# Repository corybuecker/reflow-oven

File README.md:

# reflow-oven
The plans, BoM, instructions, etc. for a soldering reflow oven. Please note that this requires an ESP32 C6 microcontroller and a thermocouple amplifier.

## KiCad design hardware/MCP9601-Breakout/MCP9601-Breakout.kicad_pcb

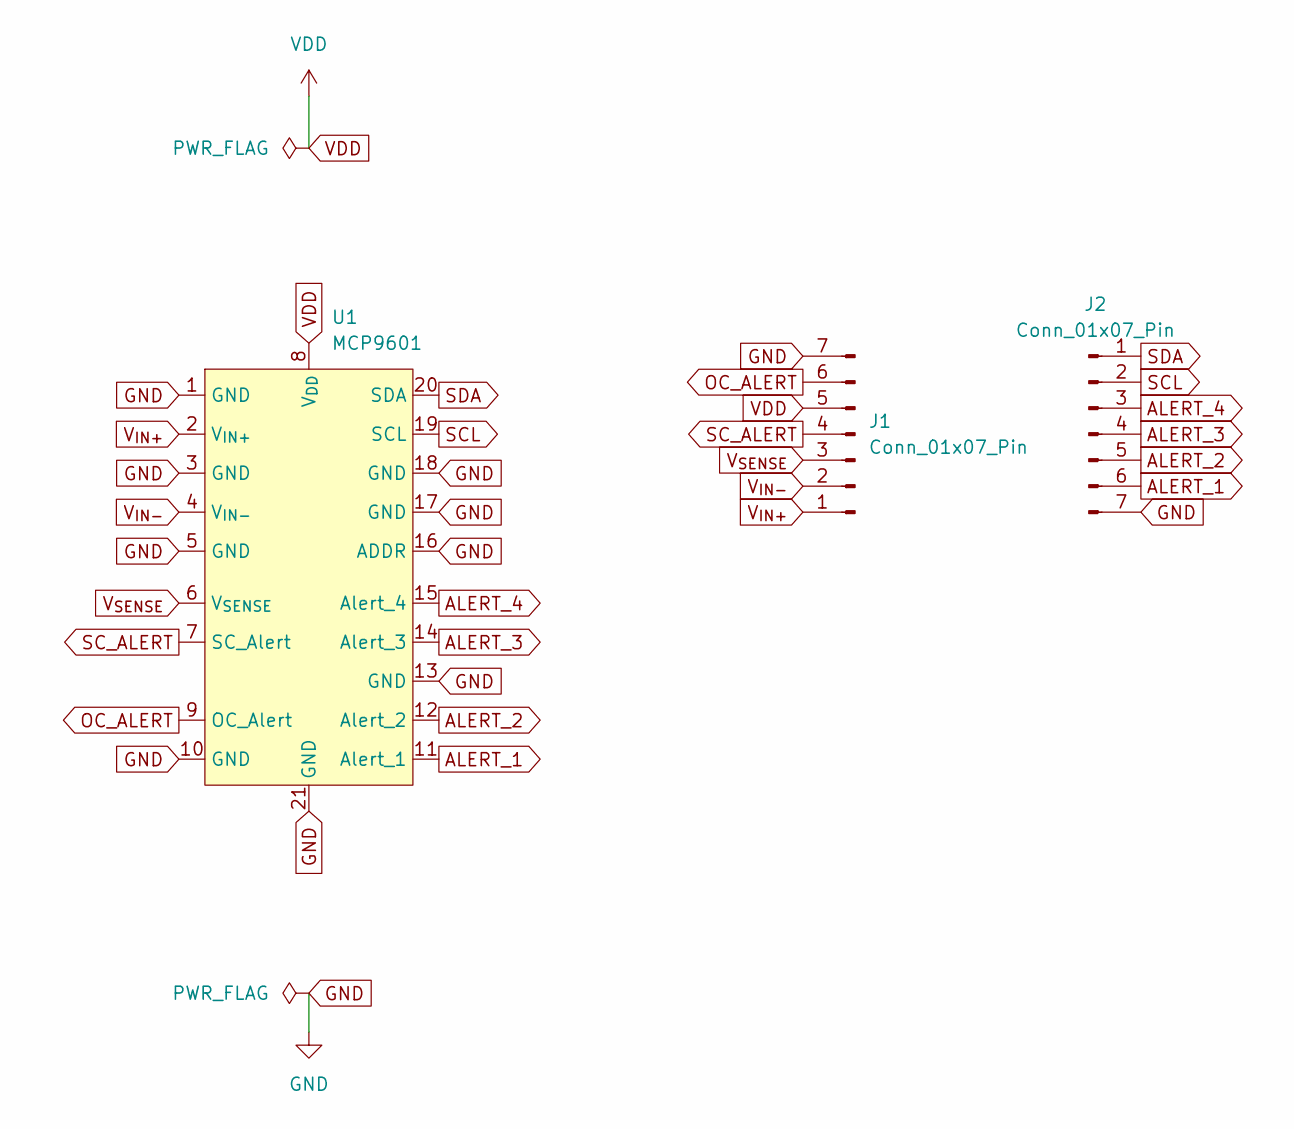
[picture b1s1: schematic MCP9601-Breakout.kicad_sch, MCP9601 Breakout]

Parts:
J1, J2: Conn_01x07_Pin; PinHeader_1x07_P2.54mm_Vertical
U1: MCP9601

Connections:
ALERT_1: J2.6, U1.11 (Alert_1)
ALERT_2: J2.5, U1.12 (Alert_2)
ALERT_3: J2.4, U1.14 (Alert_3)
ALERT_4: J2.3, U1.15 (Alert_4)
GND: J1.7, J2.7, U1.1 (GND), U1.3 (GND), U1.5 (GND), U1.10 (GND), U1.13 (GND), U1.16 (ADDR), U1.17 (GND), U1.18 (GND), U1.21 (GND)
OC_ALERT: J1.6, U1.9 (OC_Alert)
SCL: J2.2, U1.19 (SCL)
SC_ALERT: J1.4, U1.7 (SC_Alert)
SDA: J2.1, U1.20 (SDA)
VDD: J1.5, U1.8 (V_{DD})
V_{IN+}: J1.1, U1.2 (V_{IN+})
V_{IN-}: J1.2, U1.4 (V_{IN-})
V_{SENSE}: J1.3, U1.6 (V_{SENSE})

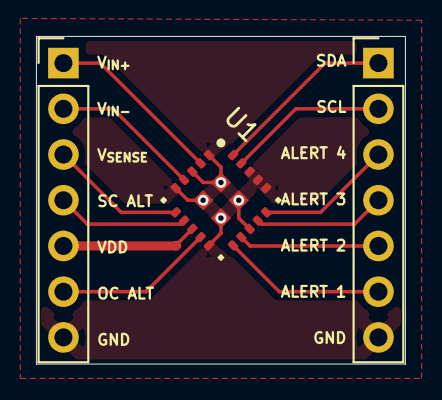
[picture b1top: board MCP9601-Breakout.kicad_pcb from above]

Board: 2 copper layers, 20.5 x 18.2 mm, 3 parts (0 on the bottom side), 13 nets.

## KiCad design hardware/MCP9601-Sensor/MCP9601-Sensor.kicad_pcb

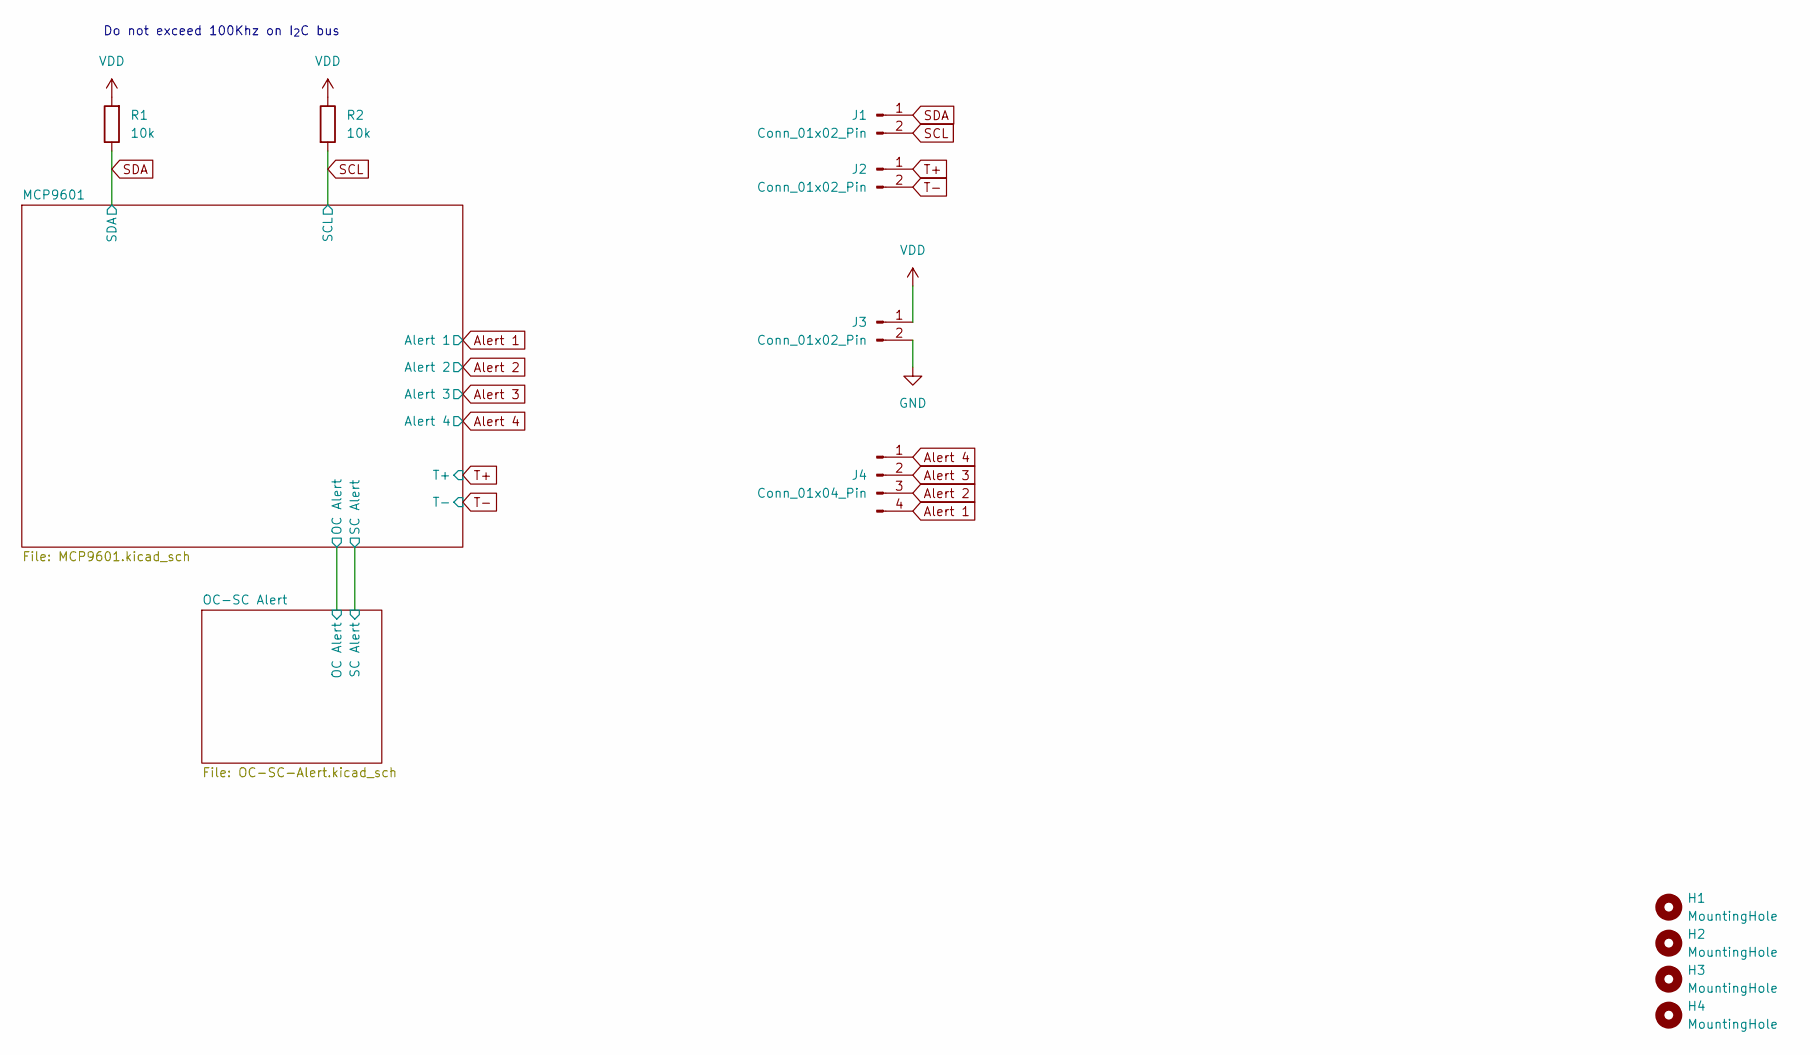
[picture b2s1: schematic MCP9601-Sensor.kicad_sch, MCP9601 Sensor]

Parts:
H1, H2, H3, H4: MountingHole; MountingHole_3.2mm_M3
J1, J2, J3: Conn_01x02_Pin; PinHeader_1x02_P2.54mm_Vertical
J4: Conn_01x04_Pin; PinHeader_1x04_P2.54mm_Vertical
R1, R2: 10k; R_0805_2012Metric; DigiKey Part Number 311-10.0KCRCT-ND

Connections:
Alert 1: J4.4; also elsewhere on the board
Alert 2: J4.3; also elsewhere on the board
Alert 3: J4.2; also elsewhere on the board
Alert 4: J4.1; also elsewhere on the board
GND: J3.2; also elsewhere on the board
SCL: J1.2, R2.2; also elsewhere on the board
SDA: J1.1, R1.1; also elsewhere on the board
T+: J2.1; also elsewhere on the board
T-: J2.2; also elsewhere on the board
VDD: J3.1, R1.2, R2.1; also elsewhere on the board

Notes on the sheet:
Do not exceed 100Khz on I_{2}C bus

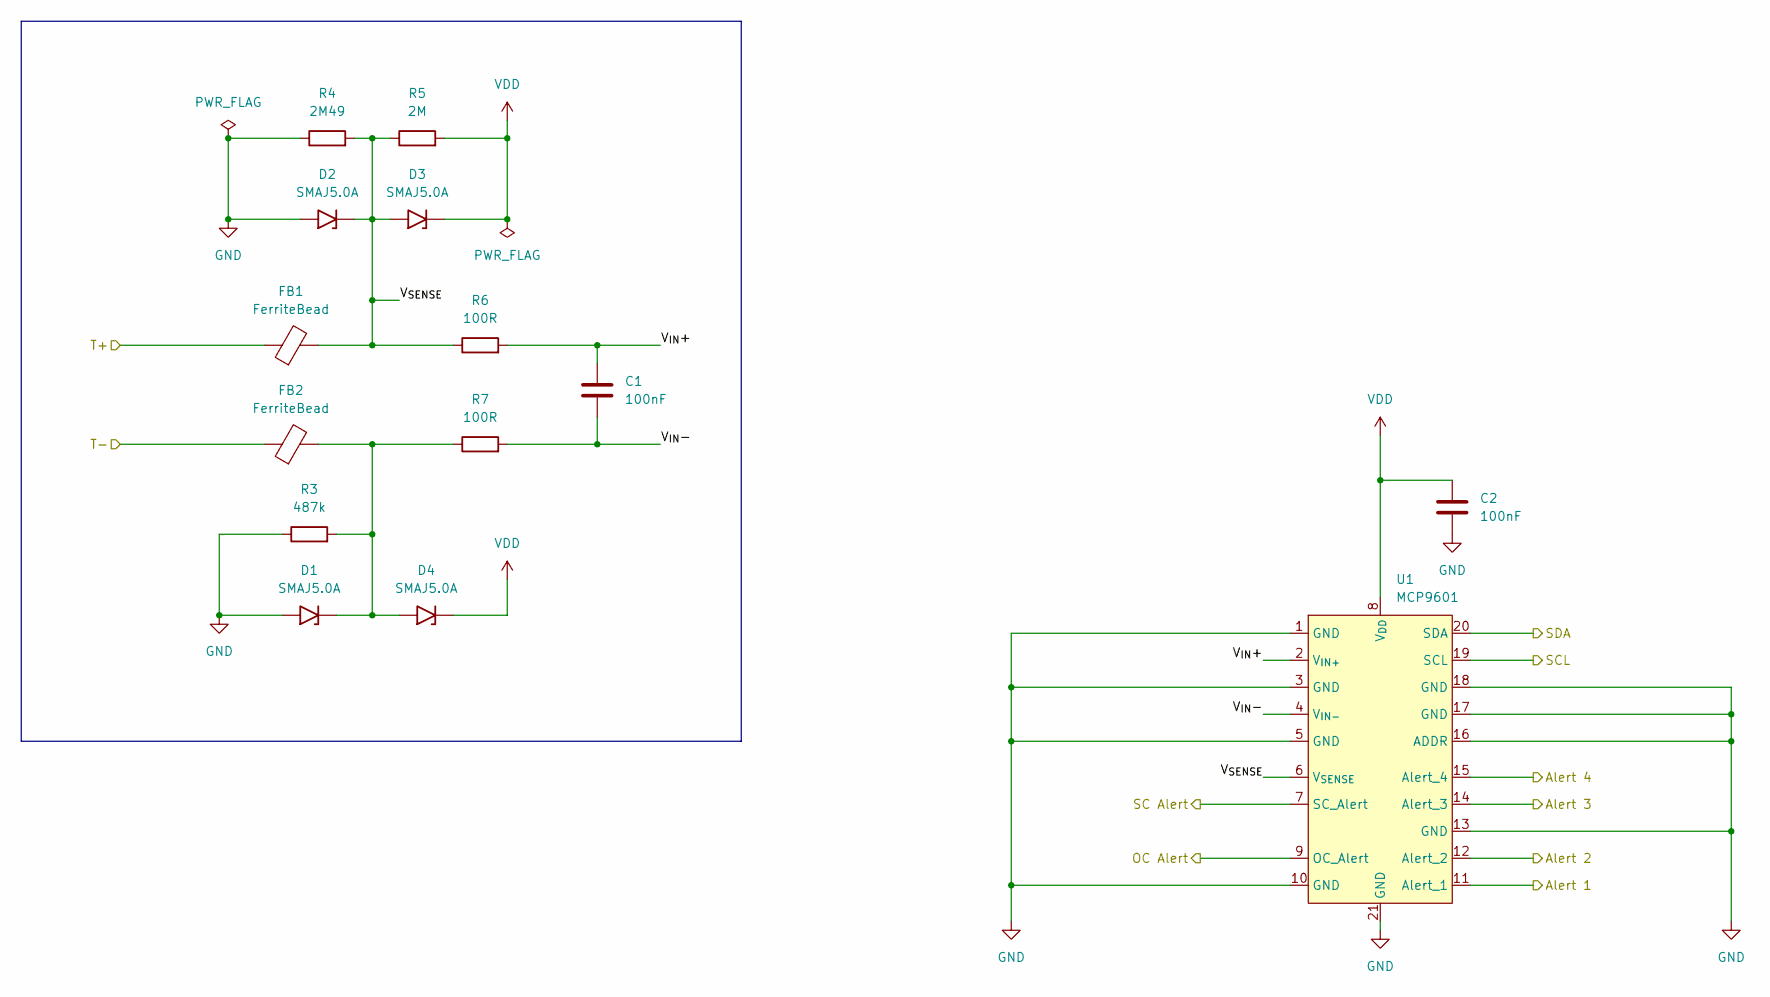
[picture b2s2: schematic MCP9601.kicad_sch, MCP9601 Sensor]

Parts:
C1, C2: 100nF; C_0805_2012Metric; DigiKey Part Number 311-1140-1-ND
D1, D2, D3, D4: SMAJ5.0A; DigiKey Part Number SMAJ5.0A-E3/61GICT-ND
FB1, FB2: FerriteBead; L_0805_2012Metric; DigiKey Part Number 240-2399-1-ND
R3: 487k; R_0805_2012Metric; DigiKey Part Number 311-487KCRCT-ND
R4: 2M49; R_0805_2012Metric; DigiKey Part Number 311-2.49MCRCT-ND
R5: 2M; R_0805_2012Metric; DigiKey Part Number 541-4129-1-ND
R6, R7: 100R; R_0805_2012Metric; DigiKey Part Number 311-100CRCT-ND
U1: MCP9601; DigiKey Part Number 150-MCP9601T-E/MXCT-ND

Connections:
/MCP9601/OC Alert: U1.9 (OC_Alert); also elsewhere on the board
/MCP9601/SC Alert: U1.7 (SC_Alert); also elsewhere on the board
/MCP9601/V_{IN}+: C1.1, R6.2, U1.2 (V_{IN+})
/MCP9601/V_{IN}-: C1.2, R7.2, U1.4 (V_{IN-})
/MCP9601/V_{SENSE}: D2.2 (Cathode), D3.1 (Anode), FB1.2, R4.2, R5.1, R6.1, U1.6 (V_{SENSE})
Alert 1: U1.11 (Alert_1); also elsewhere on the board
Alert 2: U1.12 (Alert_2); also elsewhere on the board
Alert 3: U1.14 (Alert_3); also elsewhere on the board
Alert 4: U1.15 (Alert_4); also elsewhere on the board
GND: C2.2, D1.1 (Anode), D2.1 (Anode), R3.1, R4.1, U1.1 (GND), U1.3 (GND), U1.5 (GND), U1.10 (GND), U1.13 (GND), U1.16 (ADDR), U1.17 (GND), U1.18 (GND), U1.21 (GND); also elsewhere on the board
unnamed: D1.2 (Cathode), D4.1 (Anode), FB2.2, R3.2, R7.1
SCL: U1.19 (SCL); also elsewhere on the board
SDA: U1.20 (SDA); also elsewhere on the board
T+: FB1.1; also elsewhere on the board
T-: FB2.1; also elsewhere on the board
VDD: C2.1, D3.2 (Cathode), D4.2 (Cathode), R5.2, U1.8 (V_{DD}); also elsewhere on the board

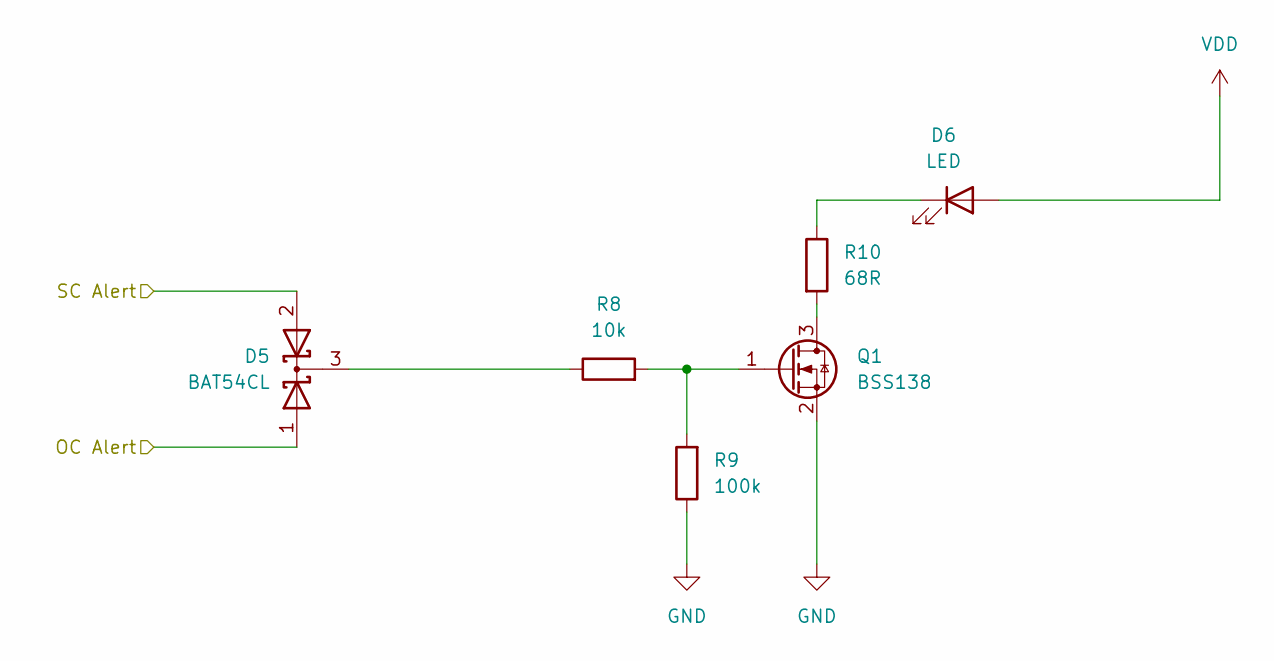
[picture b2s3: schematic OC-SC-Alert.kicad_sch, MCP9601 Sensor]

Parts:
D5: BAT54CL; DigiKey Part Number BAT54CLT3GOSCT-ND
D6: LED; LED_0805_2012Metric; DigiKey Part Number 160-1427-1-ND
Q1: BSS138; DigiKey Part Number BSS138CT-ND
R8: 10k; R_0805_2012Metric; DigiKey Part Number 311-10.0KCRCT-ND
R9: 100k; R_0805_2012Metric; DigiKey Part Number 311-100KARCT-ND
R10: 68R; R_0805_2012Metric; DigiKey Part Number 311-68ARCT-ND

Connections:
/MCP9601/OC Alert: D5.1 (A); also elsewhere on the board
/MCP9601/SC Alert: D5.2 (A); also elsewhere on the board
GND: Q1.2 (S), R9.1; also elsewhere on the board
unnamed: D5.3 (K), R8.1
unnamed: D6.1 (K), R10.1
unnamed: Q1.3 (D), R10.2
unnamed: Q1.1 (G), R8.2, R9.2
VDD: D6.2 (A); also elsewhere on the board

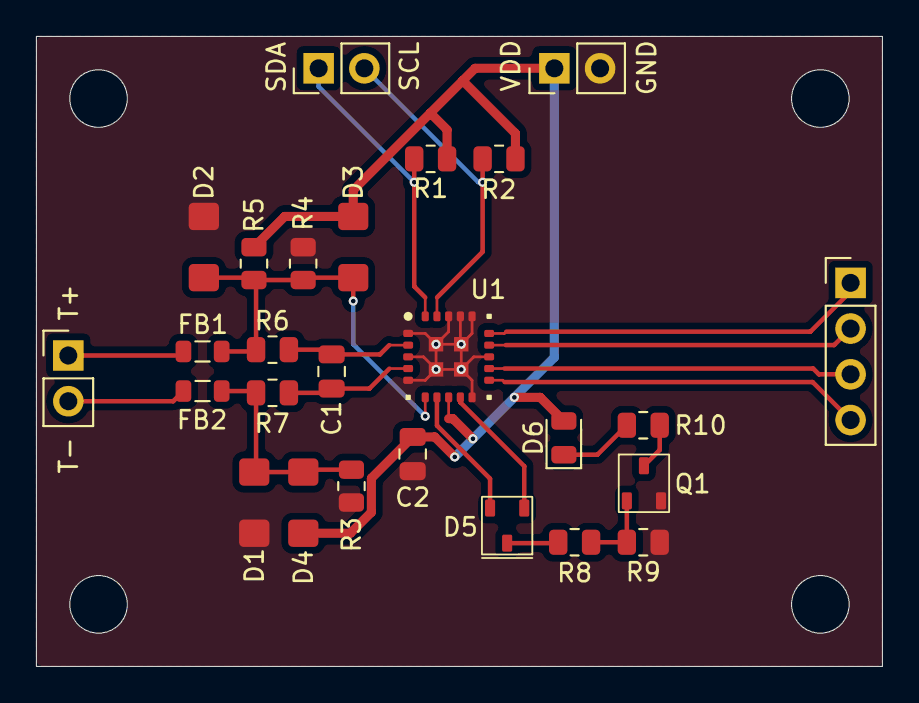
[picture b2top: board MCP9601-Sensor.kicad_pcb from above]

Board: 2 copper layers, 47.0 x 35.0 mm, 30 parts (0 on the bottom side), 20 nets.

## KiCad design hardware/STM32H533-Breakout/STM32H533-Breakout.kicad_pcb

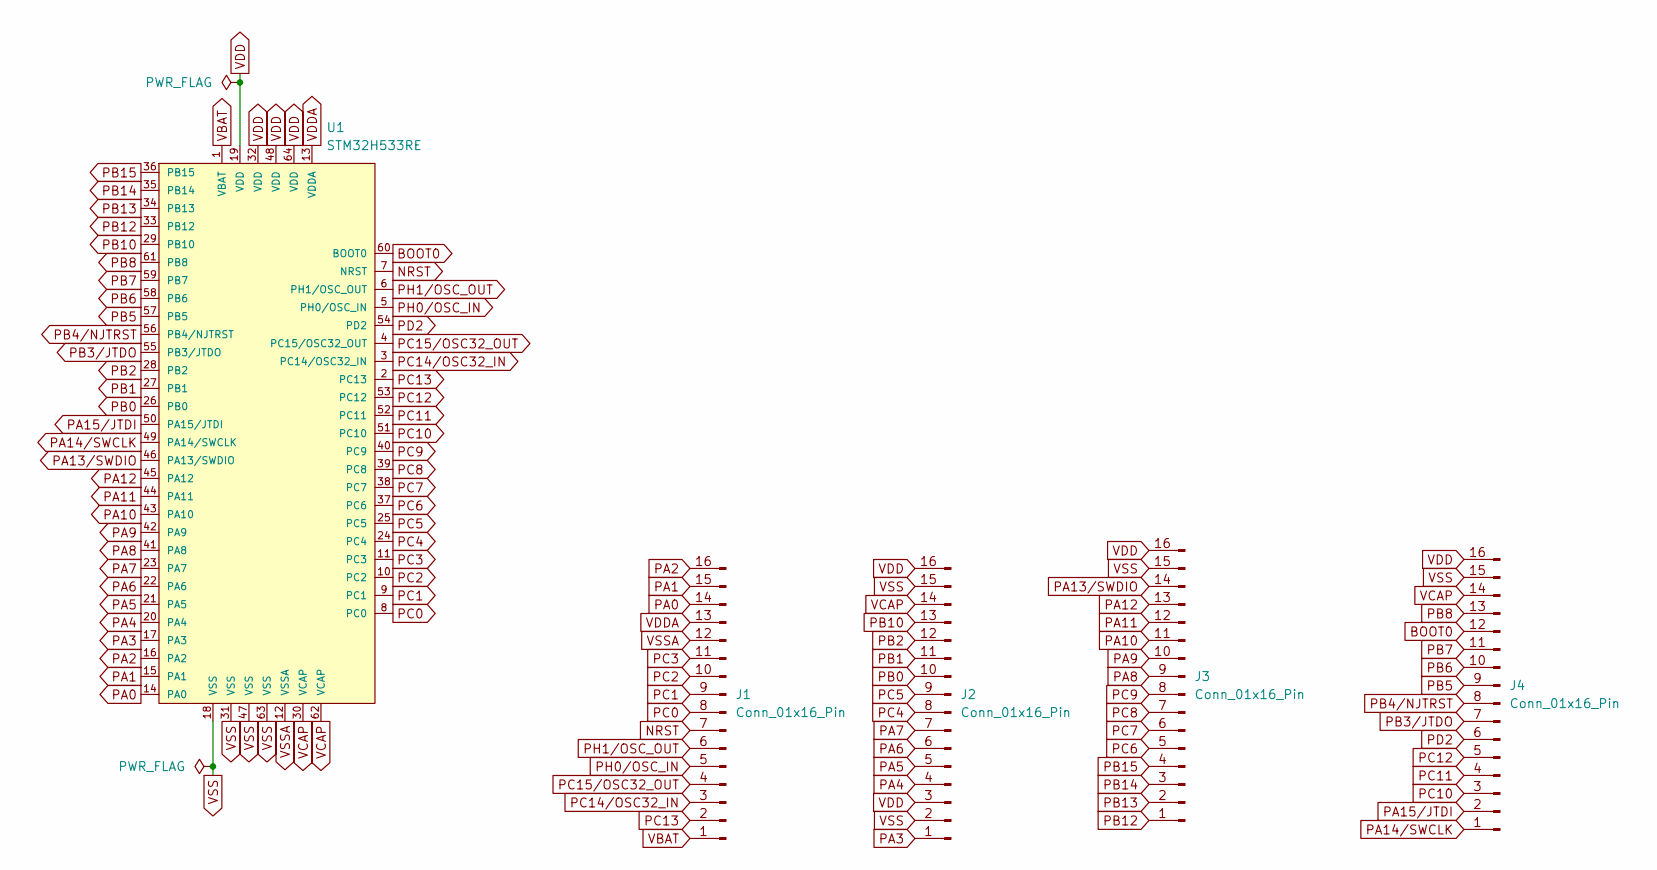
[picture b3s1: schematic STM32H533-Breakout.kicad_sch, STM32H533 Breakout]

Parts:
J1, J2, J3, J4: Conn_01x16_Pin; PinHeader_1x16_P2.54mm_Vertical
U1: STM32H533RE

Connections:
BOOT0: J4.12, U1.60 (BOOT0)
NRST: J1.7, U1.7 (NRST)
PA0: J1.14, U1.14 (PA0)
PA1: J1.15, U1.15 (PA1)
PA2: J1.16, U1.16 (PA2)
PA3: J2.1, U1.17 (PA3)
PA4: J2.4, U1.20 (PA4)
PA5: J2.5, U1.21 (PA5)
PA6: J2.6, U1.22 (PA6)
PA7: J2.7, U1.23 (PA7)
PA8: J3.9, U1.41 (PA8)
PA9: J3.10, U1.42 (PA9)
PA10: J3.11, U1.43 (PA10)
PA11: J3.12, U1.44 (PA11)
PA12: J3.13, U1.45 (PA12)
PA13/SWDIO: J3.14, U1.46 (PA13/SWDIO)
PA14/SWCLK: J4.1, U1.49 (PA14/SWCLK)
PA15/JTDI: J4.2, U1.50 (PA15/JTDI)
PB0: J2.10, U1.26 (PB0)
PB1: J2.11, U1.27 (PB1)
PB2: J2.12, U1.28 (PB2)
PB3/JTDO: J4.7, U1.55 (PB3/JTDO)
PB4/NJTRST: J4.8, U1.56 (PB4/NJTRST)
PB5: J4.9, U1.57 (PB5)
PB6: J4.10, U1.58 (PB6)
PB7: J4.11, U1.59 (PB7)
PB8: J4.13, U1.61 (PB8)
PB10: J2.13, U1.29 (PB10)
PB12: J3.1, U1.33 (PB12)
PB13: J3.2, U1.34 (PB13)
PB14: J3.3, U1.35 (PB14)
PB15: J3.4, U1.36 (PB15)
PC0: J1.8, U1.8 (PC0)
PC1: J1.9, U1.9 (PC1)
PC2: J1.10, U1.10 (PC2)
PC3: J1.11, U1.11 (PC3)
PC4: J2.8, U1.24 (PC4)
PC5: J2.9, U1.25 (PC5)
PC6: J3.5, U1.37 (PC6)
PC7: J3.6, U1.38 (PC7)
PC8: J3.7, U1.39 (PC8)
PC9: J3.8, U1.40 (PC9)
PC10: J4.3, U1.51 (PC10)
PC11: J4.4, U1.52 (PC11)
PC12: J4.5, U1.53 (PC12)
PC13: J1.2, U1.2 (PC13)
PC14/OSC32_IN: J1.3, U1.3 (PC14/OSC32_IN)
PC15/OSC32_OUT: J1.4, U1.4 (PC15/OSC32_OUT)
PD2: J4.6, U1.54 (PD2)
PH0/OSC_IN: J1.5, U1.5 (PH0/OSC_IN)
PH1/OSC_OUT: J1.6, U1.6 (PH1/OSC_OUT)
VBAT: J1.1, U1.1 (VBAT)
VCAP: J2.14, J4.14, U1.30 (VCAP), U1.62 (VCAP)
VDD: J2.3, J2.16, J3.16, J4.16, U1.19 (VDD), U1.32 (VDD), U1.48 (VDD), U1.64 (VDD)
VDDA: J1.13, U1.13 (VDDA)
VSS: J2.2, J2.15, J3.15, J4.15, U1.18 (VSS), U1.31 (VSS), U1.47 (VSS), U1.63 (VSS)
VSSA: J1.12, U1.12 (VSSA)

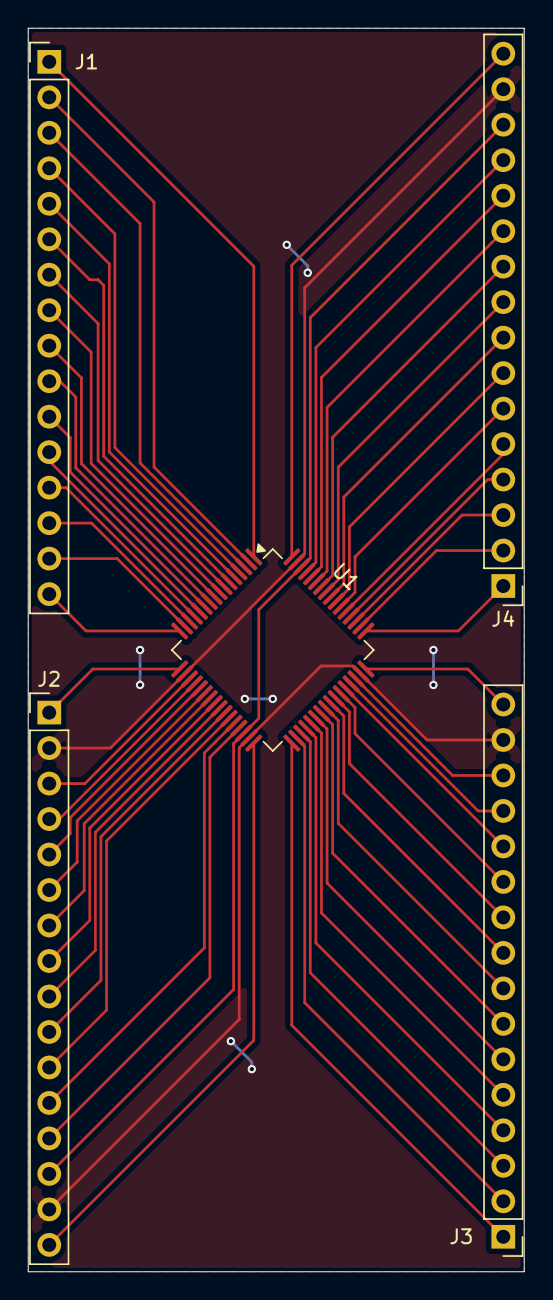
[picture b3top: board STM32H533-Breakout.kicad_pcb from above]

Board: 2 copper layers, 35.5 x 89.0 mm, 5 parts (0 on the bottom side), 57 nets.

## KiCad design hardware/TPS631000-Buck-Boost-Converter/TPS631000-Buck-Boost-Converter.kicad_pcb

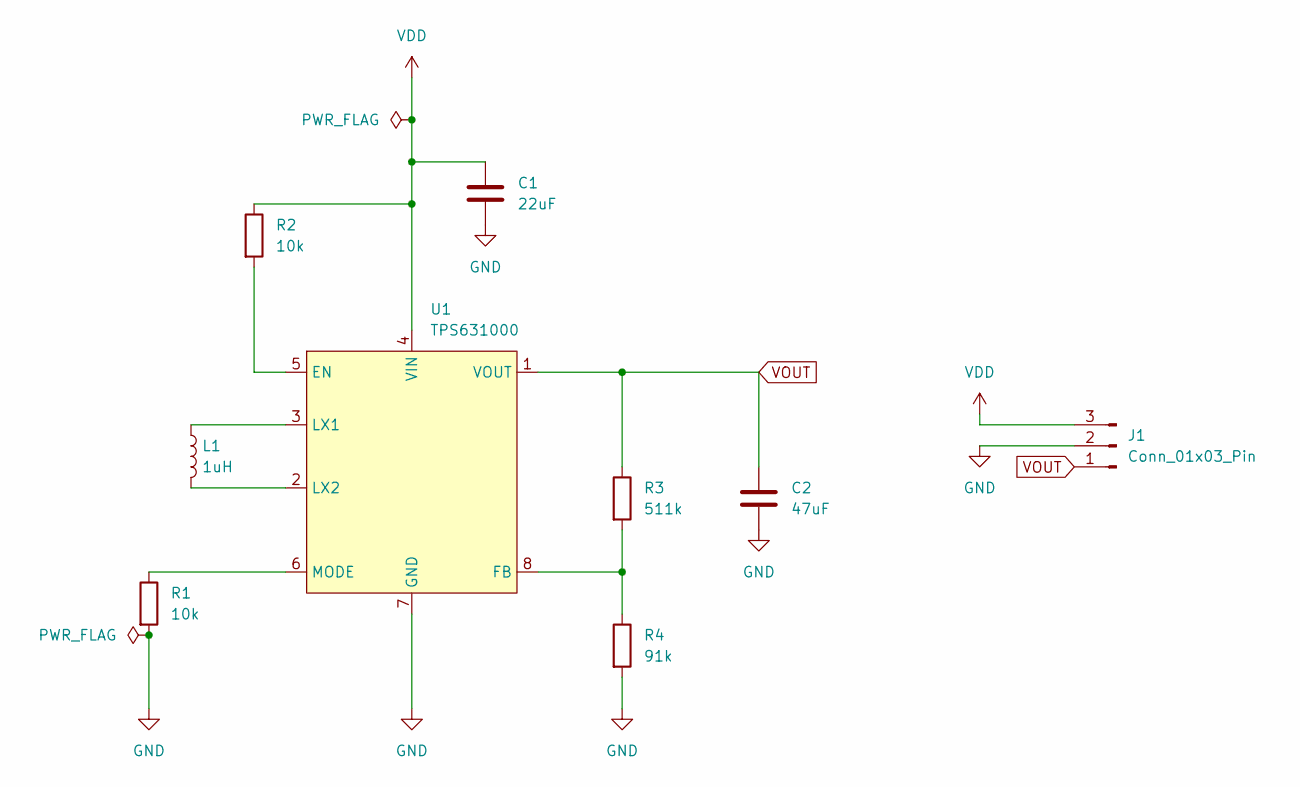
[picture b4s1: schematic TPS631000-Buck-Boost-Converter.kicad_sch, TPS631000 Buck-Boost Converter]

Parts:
C1: 22uF; C_0805_2012Metric
C2: 47uF; C_0805_2012Metric
J1: Conn_01x03_Pin; PinHeader_1x03_P2.54mm_Vertical
L1: 1uH; L_0805_2012Metric
R1, R2: 10k; R_0805_2012Metric
R3: 511k; R_0805_2012Metric
R4: 91k; R_0805_2012Metric
U1: TPS631000

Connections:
GND: C1.2, C2.2, J1.2, R1.2, R4.2, U1.7 (GND)
unnamed: R2.2, U1.5 (EN)
unnamed: R3.2, R4.1, U1.8 (FB)
unnamed: L1.1, U1.3 (LX1)
unnamed: L1.2, U1.2 (LX2)
unnamed: R1.1, U1.6 (MODE)
VDD: C1.1, J1.3, R2.1, U1.4 (VIN)
VOUT: C2.1, J1.1, R3.1, U1.1 (VOUT)

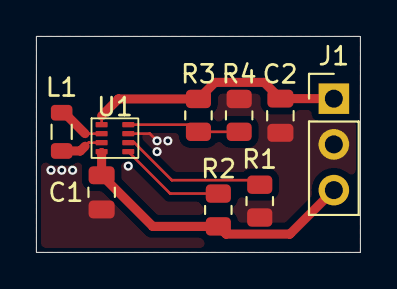
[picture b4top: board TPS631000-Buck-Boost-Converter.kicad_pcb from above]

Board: 2 copper layers, 18.0 x 12.0 mm, 9 parts (0 on the bottom side), 8 nets.

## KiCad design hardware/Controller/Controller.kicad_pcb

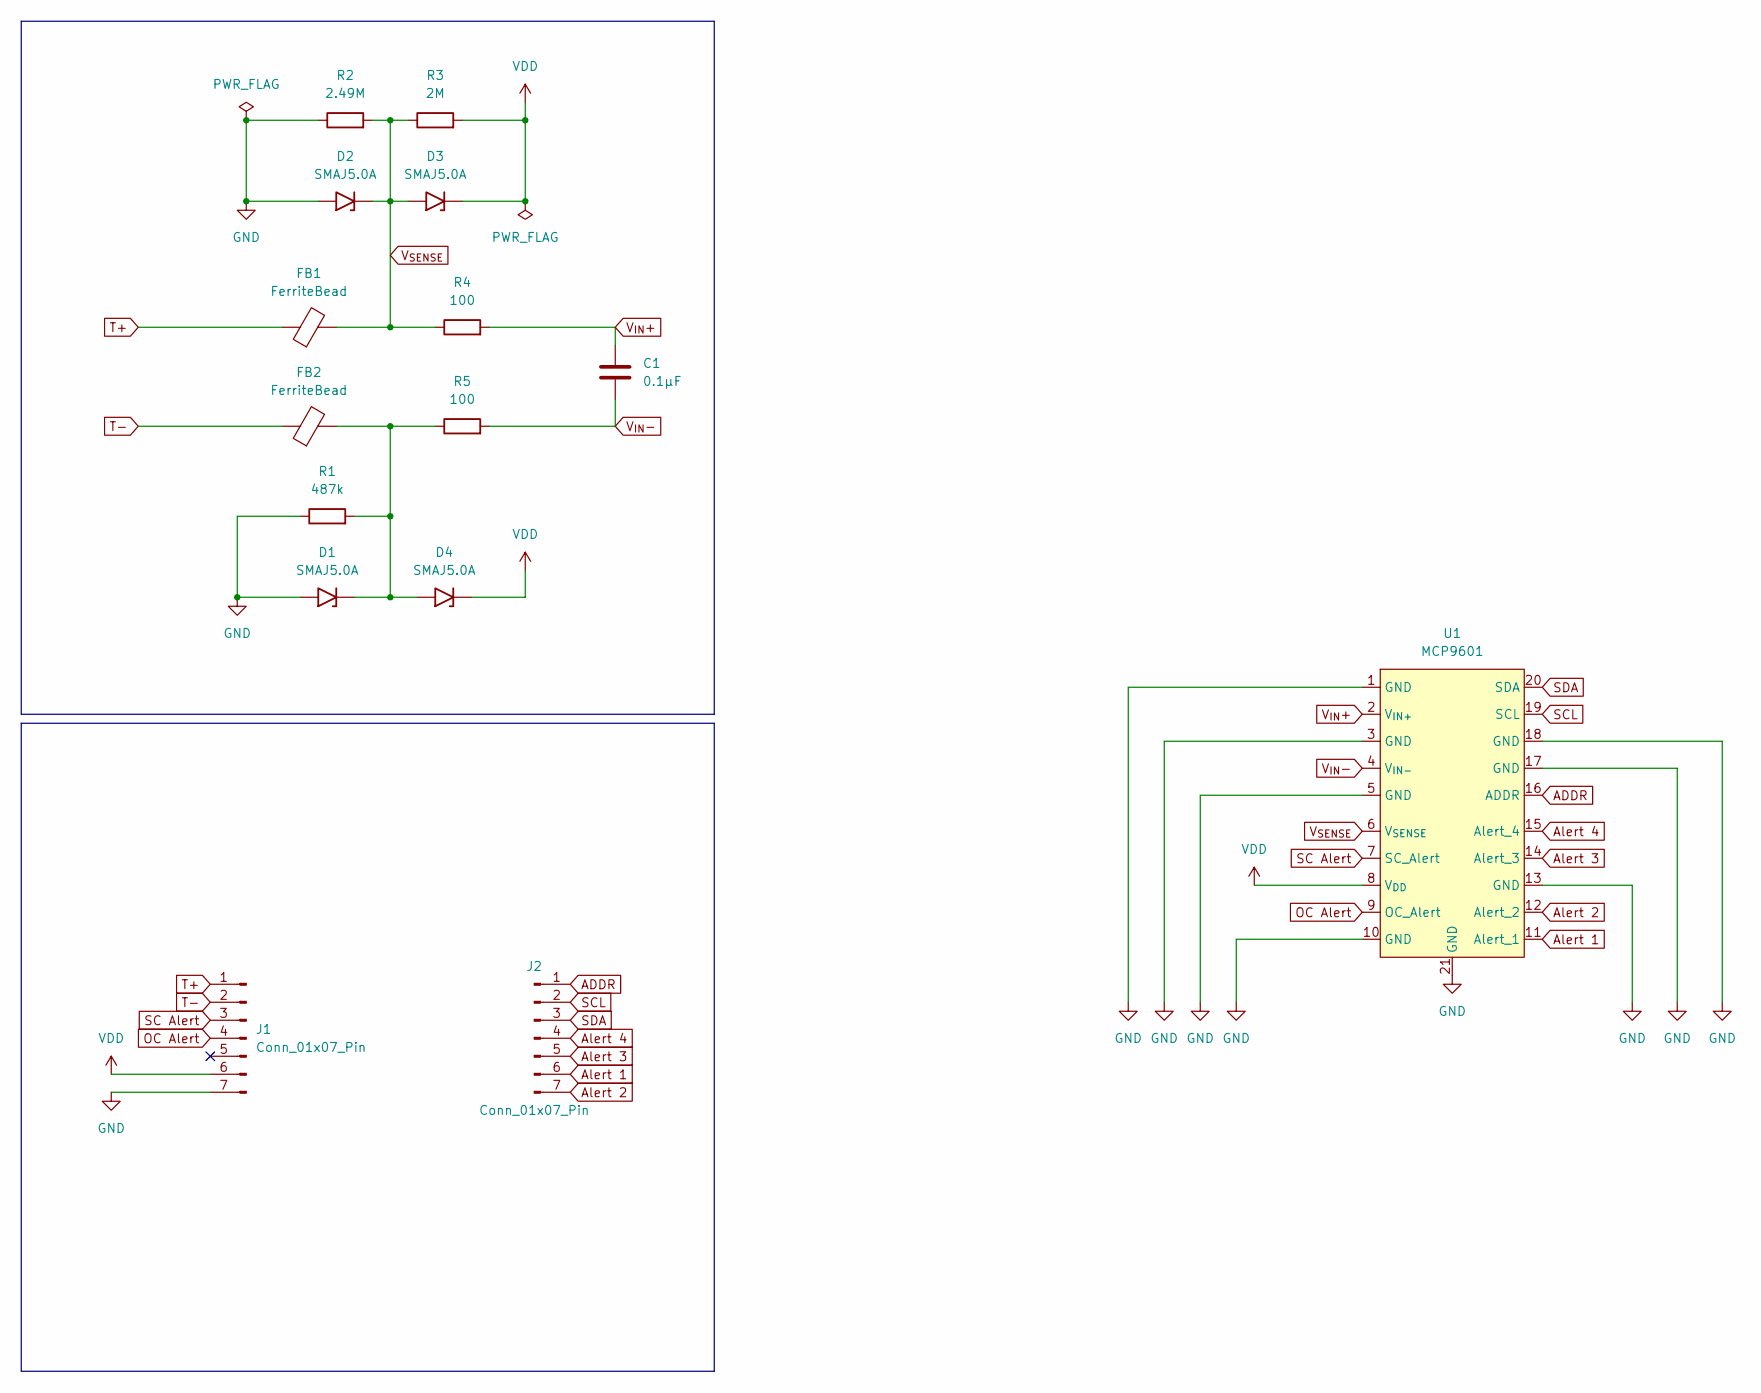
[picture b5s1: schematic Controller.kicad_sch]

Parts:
C1: 0.1μF; C_0805_2012Metric; DigiKey Part Number 311-1140-1-ND
D1, D2, D3, D4: SMAJ5.0A
FB1, FB2: FerriteBead; L_0805_2012Metric; DigiKey Part Number 240-2399-1-ND
J1, J2: Conn_01x07_Pin; PinHeader_1x07_P2.54mm_Vertical
R1: 487k; R_0805_2012Metric; DigiKey Part Number 311-487KCRCT-ND
R2: 2.49M; R_0805_2012Metric; DigiKey Part Number 311-2.49MCRCT-ND
R3: 2M; R_0805_2012Metric; DigiKey Part Number 541-4129-1-ND
R4, R5: 100; R_0805_2012Metric; DigiKey Part Number 311-100CRCT-ND
U1: MCP9601

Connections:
ADDR: J2.1, U1.16 (ADDR)
Alert 1: J2.6, U1.11 (Alert_1)
Alert 2: J2.7, U1.12 (Alert_2)
Alert 3: J2.5, U1.14 (Alert_3)
Alert 4: J2.4, U1.15 (Alert_4)
GND: D1.1 (Anode), D2.1 (Anode), J1.7, R1.1, R2.1, U1.1 (GND), U1.3 (GND), U1.5 (GND), U1.10 (GND), U1.13 (GND), U1.17 (GND), U1.18 (GND), U1.21 (GND)
unnamed: D1.2 (Cathode), D4.1 (Anode), FB2.2, R1.2, R5.1
OC Alert: J1.4, U1.9 (OC_Alert)
SC Alert: J1.3, U1.7 (SC_Alert)
SCL: J2.2, U1.19 (SCL)
SDA: J2.3, U1.20 (SDA)
T+: FB1.1, J1.1
T-: FB2.1, J1.2
VDD: D3.2 (Cathode), D4.2 (Cathode), J1.6, R3.2, U1.8 (V_{DD})
V_{IN}+: C1.1, R4.2, U1.2 (V_{IN+})
V_{IN}-: C1.2, R5.2, U1.4 (V_{IN-})
V_{SENSE}: D2.2 (Cathode), D3.1 (Anode), FB1.2, R2.2, R3.1, R4.1, U1.6 (V_{SENSE})

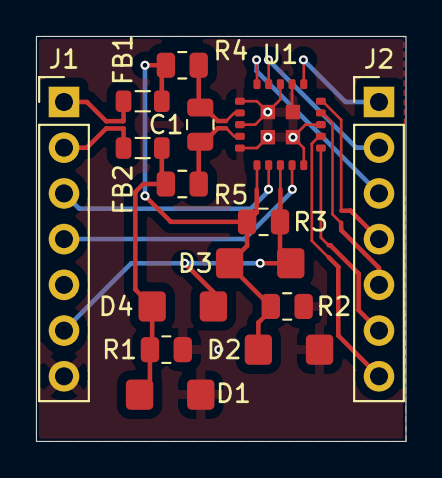
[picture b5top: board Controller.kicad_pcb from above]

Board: 2 copper layers, 20.5 x 22.5 mm, 15 parts (0 on the bottom side), 17 nets.

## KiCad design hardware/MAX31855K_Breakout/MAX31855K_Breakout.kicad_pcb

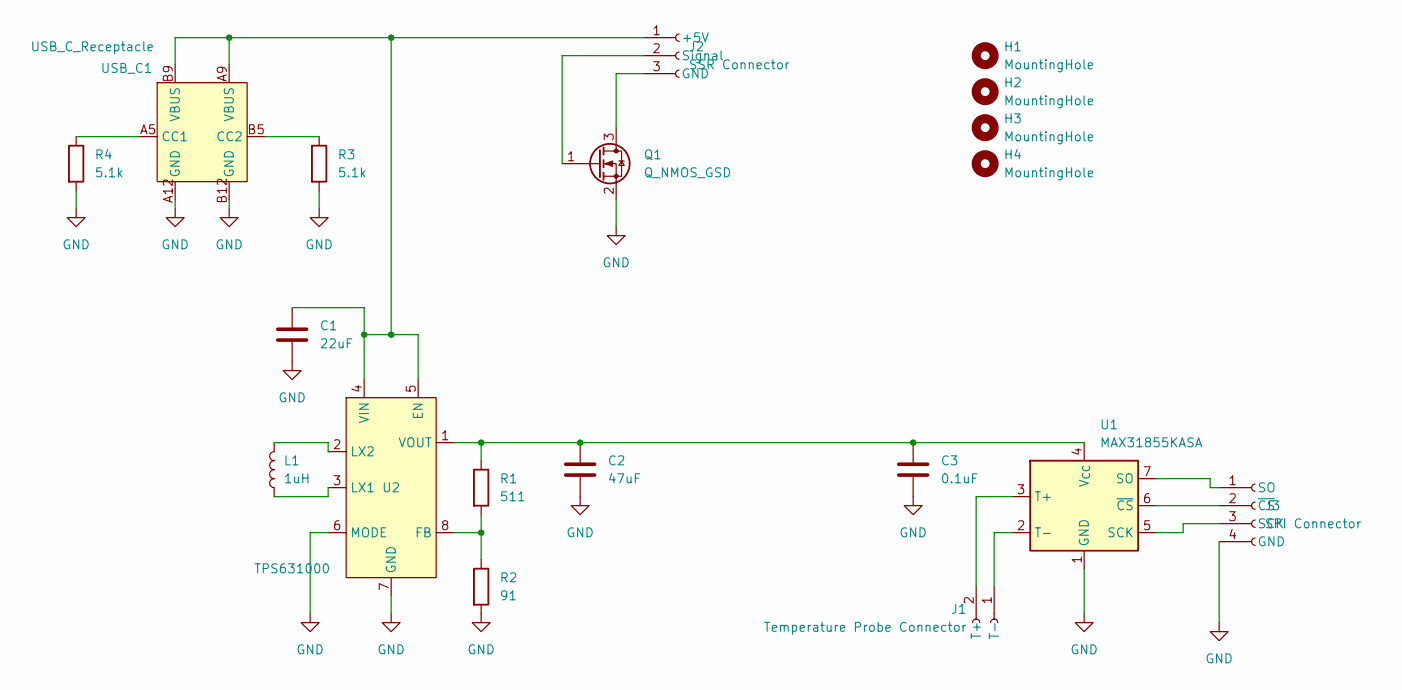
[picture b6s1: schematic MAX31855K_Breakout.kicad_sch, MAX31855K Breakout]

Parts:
C1: 22uF; C_0805_2012Metric; DigiKey Part Number 490-GRM21BZ71A226ME15LCT-ND
C2: 47uF; C_0805_2012Metric; DigiKey Part Number 490-9961-1-ND
C3: 0.1uF; C_0805_2012Metric; DigiKey Part Number 311-1140-1-ND
H1, H2, H3, H4: MountingHole; MountingHole_3.2mm_M3
J1: Temperature Probe Connector; JST_XH_B2B-XH-A_1x02_P2.50mm_Vertical; DigiKey Part Number 455-B2B-XH-A-ND
J2: SSR Connector; JST_XH_B3B-XH-A_1x03_P2.50mm_Vertical; DigiKey Part Number 455-2248-ND
J3: SPI Connector; JST_XH_B4B-XH-A_1x04_P2.50mm_Vertical; DigiKey Part Number 455-B4B-XH-A-ND
L1: 1uH; L_0805_2012Metric; DigiKey Part Number 541-IHHP0805ZHER1R0M01CT-ND
Q1: Q_NMOS_GSD; SOT-23-3; DigiKey Part Number 2N7002NCT-ND
R1: 511; R_0805_2012Metric; DigiKey Part Number 311-511CRCT-ND
R2: 91; R_0805_2012Metric; DigiKey Part Number P91.0CCT-ND
R3, R4: 5.1k; R_0805_2012Metric; DigiKey Part Number 311-5.1KARCT-ND
U1: MAX31855KASA; SOIC-8_3.9x4.9mm_P1.27mm; DigiKey Part Number MAX31855KASA+TCT-ND
U2: TPS631000; SOT-583-8
USB_C1: USB_C_Receptacle; DigiKey Part Number 900-2171750001CT-ND

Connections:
GND: C1.2, C2.1, C3.1, J3.4 (GND), Q1.2 (S), R2.2, R3.2, R4.2, U1.1 (GND), U2.6 (MODE), U2.7 (GND), USB_C1.A12 (GND), USB_C1.B12 (GND), USB_C1.S1 (Shield)
unnamed: J1.2 (T+), U1.3 (T+)
unnamed: J1.1 (T-), U1.2 (T-)
unnamed: C1.1, J2.1 (+5V), U2.4 (VIN), U2.5 (EN), USB_C1.A9 (VBUS), USB_C1.B9 (VBUS)
unnamed: J2.3 (GND), Q1.3 (D)
unnamed: J2.2 (Signal), Q1.1 (G)
unnamed: J3.3 (SCK), U1.5 (SCK)
unnamed: J3.1 (SO), U1.7 (SO)
unnamed: J3.2 (~CS), U1.6 (~CS)
unnamed: C2.2, C3.2, R1.1, U1.4 (V_{CC}), U2.1 (VOUT)
unnamed: R1.2, R2.1, U2.8 (FB)
unnamed: L1.1, U2.3 (LX1)
unnamed: L1.2, U2.2 (LX2)
unnamed: R4.1, USB_C1.A5 (CC1)
unnamed: R3.1, USB_C1.B5 (CC2)

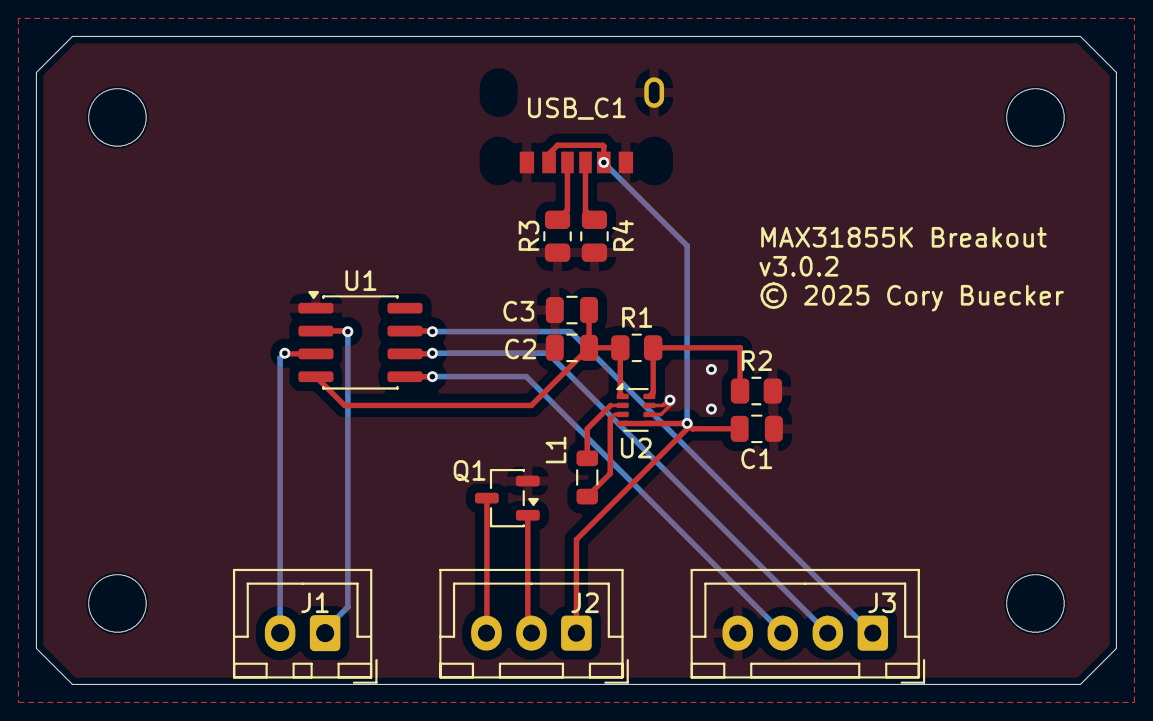
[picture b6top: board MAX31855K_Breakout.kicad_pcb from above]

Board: 2 copper layers, 60.0 x 36.0 mm, 19 parts (0 on the bottom side), 15 nets.

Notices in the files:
hardware/MAX31855K_Breakout/MAX31855K_Breakout.kicad_pcb:
© 2025 Stanton Cory Buecker
© 2025 Cory Buecker
